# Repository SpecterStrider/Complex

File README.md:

# Project COMPLEX
Complex is a 36-key ergonomic split keyboard inspired by  

Corne by foostan and  
https://github.com/foostan/crkbd/tree/main

Tempest by thrly  
https://github.com/thrly/tempest

## TO DO List
- [ ] Impedance match USB
- [ ] Right Side PCB
- [ ] include Case and 3d files
- [ ] Rebase from kiCAD to Fusion ECAD
- [ ] Begin QMK firmware
- [ ] define COMPLEX.cpp in QMK environment
- [ ] create Keyamp

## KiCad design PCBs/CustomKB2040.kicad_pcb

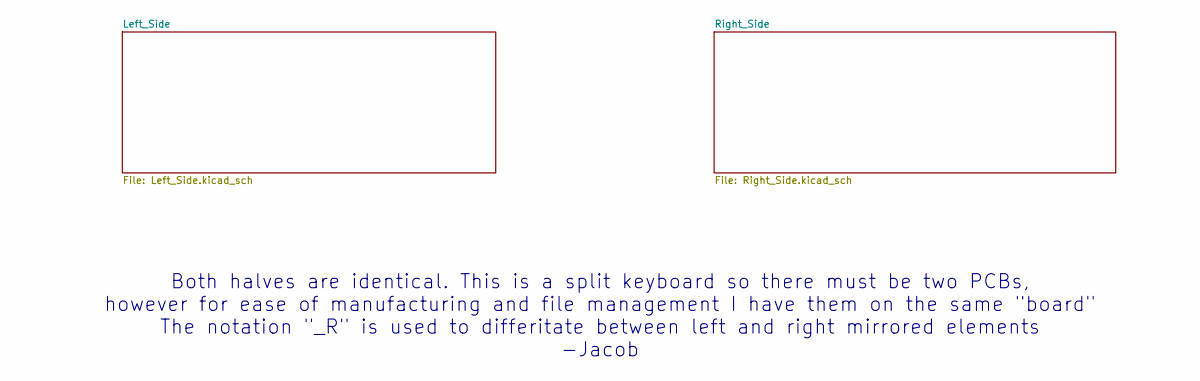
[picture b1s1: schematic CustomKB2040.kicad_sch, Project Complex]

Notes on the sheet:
Both halves are identical. This is a split keyboard so there must be two PCBs, however for ease of manufacturing and file management I have them on the same "board" The notation "_R" is used to differitate between left and right mirrored elements -Jacob

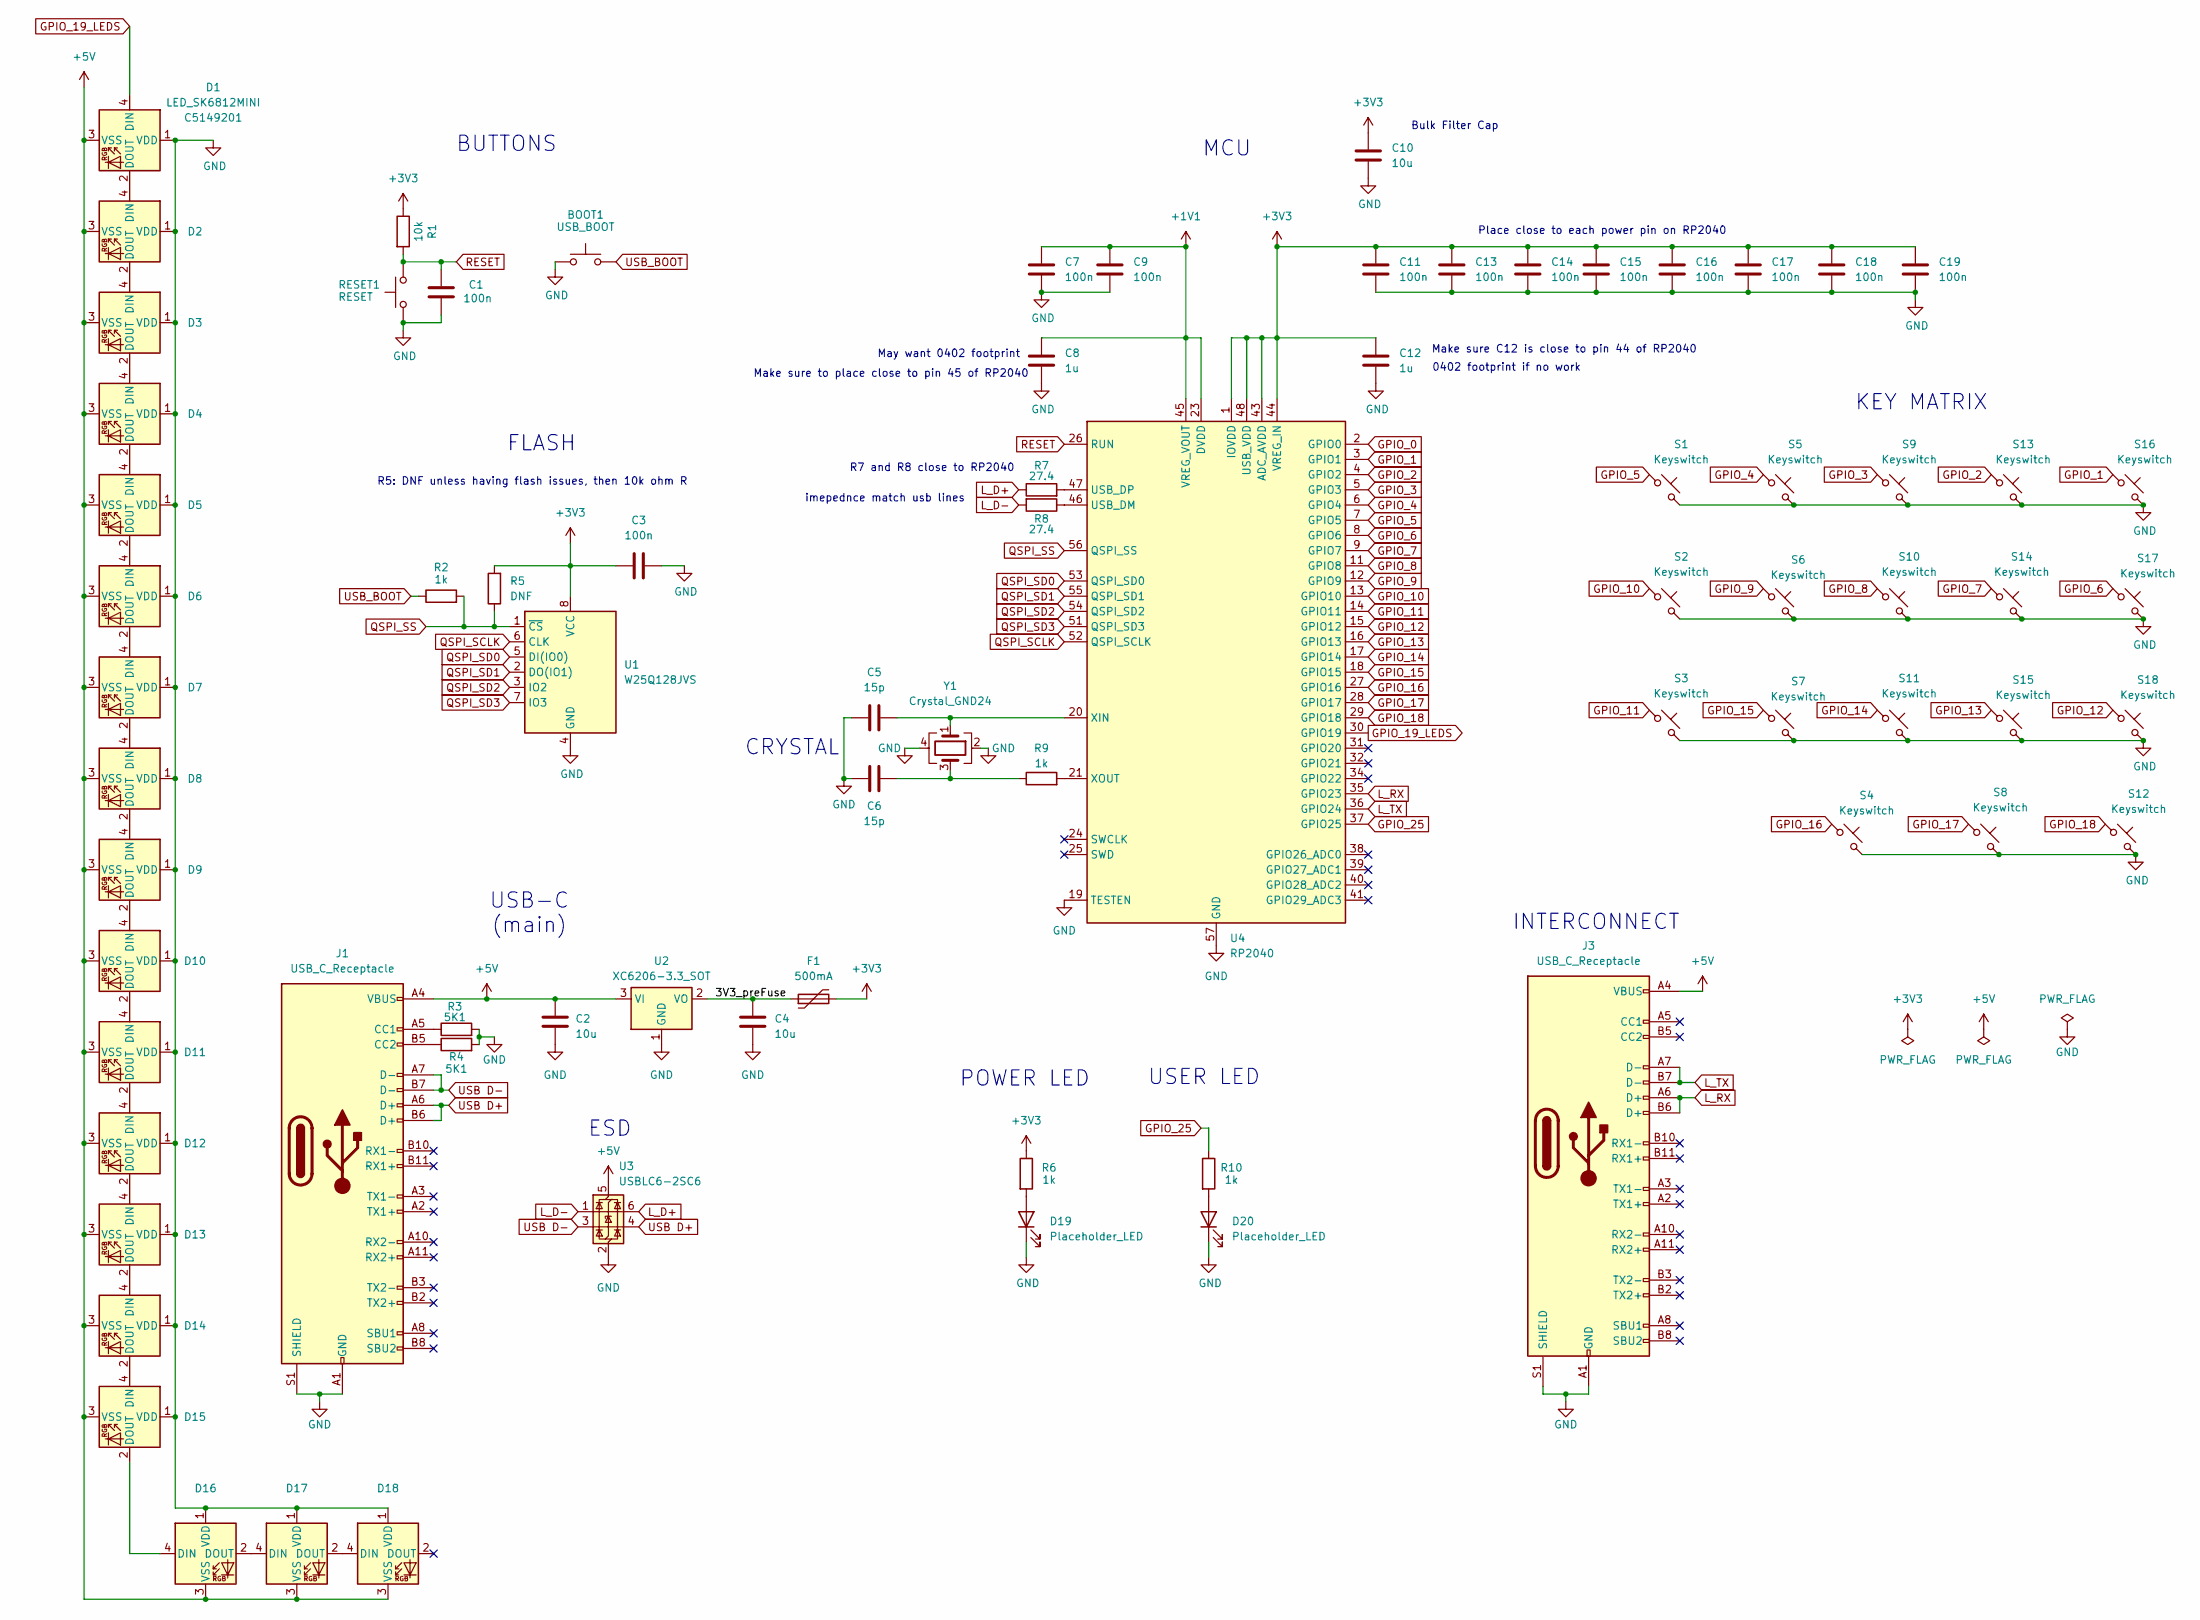
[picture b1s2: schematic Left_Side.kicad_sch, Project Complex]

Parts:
BOOT1: USB_BOOT; SW_Push_1P1T_NO_CK_KMR2
C1, C3, C7, C9, C11, C13, C14, C15, C16, C17, C18, C19: 100n; C_0603_1608Metric
C2, C4, C10: 10u; C_0603_1608Metric
C5, C6: 15p; C_0603_1608Metric
C8, C12: 1u; C_0603_1608Metric
D1, D2, D3, D4, D5, D6, D7, D8, D9, D10, D11, D12, D13, D14, D15, D16, D17, D18: LED_SK6812MINI; LCSC C5149201
D19, D20: Placeholder_LED; LED_0805
F1: 500mA; Fuse_0603
J1, J3: USB_C_Receptacle; USB_C_Receptacle_HRO_TYPE-C-31-M-12
R1: 10k; R_0603_1608Metric
R2, R6, R9, R10: 1k; R_0603_1608Metric
R3, R4: 5K1; R_0603_1608Metric
R5: DNF; R_0603_1608Metric
R7, R8: 27.4; R_0603_1608Metric
RESET1: RESET; SW_Push_1P1T_NO_CK_KMR2
S1, S2, S3, S4, S5, S6, S7, S8, S9, S10, S11, S12, S13, S14, S15, S16, S17, S18: Keyswitch; Hotswap_Choc_V2_Plated_1.00u
U1: W25Q128JVS; SOIC-8_5.23x5.23mm_P1.27mm
U2: XC6206-3.3_SOT; Voltage_SOT-23
U3: USBLC6-2SC6; SOT-23-6
U4: RP2040; QFN-56-1EP_7x7mm_P0.4mm_EP3.2x3.2mm
Y1: Crystal_GND24; Crystal_SMD_Abracon_ABM8G-4Pin_3.2x2.5mm

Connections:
+1V1: C7.1, C8.1, C9.1, U4.23 (DVDD), U4.45 (VREG_VOUT), U4.50 (DVDD)
+3V3: C3.1, C10.1, C11.1, C12.1, C13.1, C14.1, C15.1, C16.1, C17.1, C18.1, C19.1, F1.2, R1.1, R5.2, R6.1, U1.8 (VCC), U4.1 (IOVDD), U4.10 (IOVDD), U4.22 (IOVDD), U4.33 (IOVDD), U4.42 (IOVDD), U4.43 (ADC_AVDD), U4.44 (VREG_IN), U4.48 (USB_VDD), U4.49 (IOVDD)
+5V: C2.1, D1.3 (VSS), D2.3 (VSS), D3.3 (VSS), D4.3 (VSS), D5.3 (VSS), D6.3 (VSS), D7.3 (VSS), D8.3 (VSS), D9.3 (VSS), D10.3 (VSS), D11.3 (VSS), D12.3 (VSS), D13.3 (VSS), D14.3 (VSS), D15.3 (VSS), D16.3 (VSS), D17.3 (VSS), D18.3 (VSS), J1.A4 (VBUS), J1.A9 (VBUS), J1.B4 (VBUS), J1.B9 (VBUS), J3.A4 (VBUS), J3.A9 (VBUS), J3.B4 (VBUS), J3.B9 (VBUS), U2.3 (VI), U3.5 (VBUS)
/Left_Side/3V3_preFuse: C4.1, F1.1, U2.2 (VO)
GND: BOOT1.1, C1.1, C2.2, C3.2, C4.2, C5.2, C6.2, C7.2, C8.2, C9.2, C10.2, C11.2, C12.2, C13.2, C14.2, C15.2, C16.2, C17.2, C18.2, C19.2, D1.1 (VDD), D2.1 (VDD), D3.1 (VDD), D4.1 (VDD), D5.1 (VDD), D6.1 (VDD), D7.1 (VDD), D8.1 (VDD), D9.1 (VDD), D10.1 (VDD), D11.1 (VDD), D12.1 (VDD), D13.1 (VDD), D14.1 (VDD), D15.1 (VDD), D16.1 (VDD), D17.1 (VDD), D18.1 (VDD), D19.1 (K), D20.1 (K), J1.A1 (GND), J1.A12 (GND), J1.B1 (GND), J1.B12 (GND), J1.S1 (SHIELD), J3.A1 (GND), J3.A12 (GND), J3.B1 (GND), J3.B12 (GND), J3.S1 (SHIELD), R3.2, R4.2, RESET1.1, S1.2, S2.2, S3.2, S4.2, S5.2, S6.2, S7.2, S8.2, S9.2, S10.2, S11.2, S12.2, S13.2, S14.2, S15.2, S16.2, S17.2, S18.2, U1.4 (GND), U2.1 (GND), U3.2 (GND), U4.19 (TESTEN), U4.57 (GND), Y1.2, Y1.4
GPIO_0: U4.2 (GPIO0)
GPIO_1: S16.1, U4.3 (GPIO1)
GPIO_2: S13.1, U4.4 (GPIO2)
GPIO_3: S9.1, U4.5 (GPIO3)
GPIO_4: S5.1, U4.6 (GPIO4)
GPIO_5: S1.1, U4.7 (GPIO5)
GPIO_6: S17.1, U4.8 (GPIO6)
GPIO_7: S14.1, U4.9 (GPIO7)
GPIO_8: S10.1, U4.11 (GPIO8)
GPIO_9: S6.1, U4.12 (GPIO9)
GPIO_10: S2.1, U4.13 (GPIO10)
GPIO_11: S3.1, U4.14 (GPIO11)
GPIO_12: S18.1, U4.15 (GPIO12)
GPIO_13: S15.1, U4.16 (GPIO13)
GPIO_14: S11.1, U4.17 (GPIO14)
GPIO_15: S7.1, U4.18 (GPIO15)
GPIO_16: S4.1, U4.27 (GPIO16)
GPIO_17: S8.1, U4.28 (GPIO17)
GPIO_18: S12.1, U4.29 (GPIO18)
GPIO_19_LEDS: D1.4 (DIN), U4.30 (GPIO19)
GPIO_25: R10.1, U4.37 (GPIO25)
L_D+: R7.1, U3.6 (I/O1)
L_D-: R8.2, U3.1 (I/O1)
L_RX: J3.A6 (D+), J3.B6 (D+), U4.35 (GPIO23)
L_TX: J3.A7 (D-), J3.B7 (D-), U4.36 (GPIO24)
unnamed: C6.1, R9.1, Y1.3
unnamed: D1.2 (DOUT), D2.4 (DIN)
unnamed: D2.2 (DOUT), D3.4 (DIN)
unnamed: D3.2 (DOUT), D4.4 (DIN)
unnamed: D4.2 (DOUT), D5.4 (DIN)
unnamed: D5.2 (DOUT), D6.4 (DIN)
unnamed: D6.2 (DOUT), D7.4 (DIN)
unnamed: D7.2 (DOUT), D8.4 (DIN)
unnamed: D8.2 (DOUT), D9.4 (DIN)
unnamed: D9.2 (DOUT), D10.4 (DIN)
unnamed: D10.2 (DOUT), D11.4 (DIN)
unnamed: D11.2 (DOUT), D12.4 (DIN)
unnamed: D12.2 (DOUT), D13.4 (DIN)
unnamed: D13.2 (DOUT), D14.4 (DIN)
unnamed: D14.2 (DOUT), D15.4 (DIN)
unnamed: D15.2 (DOUT), D16.4 (DIN)
unnamed: D16.2 (DOUT), D17.4 (DIN)
unnamed: D17.2 (DOUT), D18.4 (DIN)
unnamed: D19.2 (A), R6.2
unnamed: D20.2 (A), R10.2
unnamed: J1.A5 (CC1), R3.1
unnamed: J1.B5 (CC2), R4.1
unnamed: R8.1, U4.46 (USB_DM)
unnamed: R7.2, U4.47 (USB_DP)
unnamed: C5.1, U4.20 (XIN), Y1.1
unnamed: R9.2, U4.21 (XOUT)
QSPI_SCLK: U1.6 (CLK), U4.52 (QSPI_SCLK)
QSPI_SD0: U1.5 (DI(IO0)), U4.53 (QSPI_SD0)
QSPI_SD1: U1.2 (DO(IO1)), U4.55 (QSPI_SD1)
QSPI_SD2: U1.3 (IO2), U4.54 (QSPI_SD2)
QSPI_SD3: U1.7 (IO3), U4.51 (QSPI_SD3)
QSPI_SS: R2.2, R5.1, U1.1 (~CS), U4.56 (QSPI_SS)
RESET: C1.2, R1.2, RESET1.2, U4.26 (RUN)
USB D+: J1.A6 (D+), J1.B6 (D+), U3.4 (I/O2)
USB D-: J1.A7 (D-), J1.B7 (D-), U3.3 (I/O2)
USB_BOOT: BOOT1.2, R2.1

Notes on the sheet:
MCU
Bulk Filter Cap
Make sure C12 is close to pin 44 of RP2040
USER LED
POWER LED
FLASH
ESD
R7 and R8 close to RP2040
CRYSTAL
May want 0402 footprint
INTERCONNECT
BUTTONS
Make sure to place close to pin 45 of RP2040
R5: DNF unless having flash issues, then 10k ohm R
imepednce match usb lines
USB-C (main)
0402 footprint if no work
Place close to each power pin on RP2040
KEY MATRIX

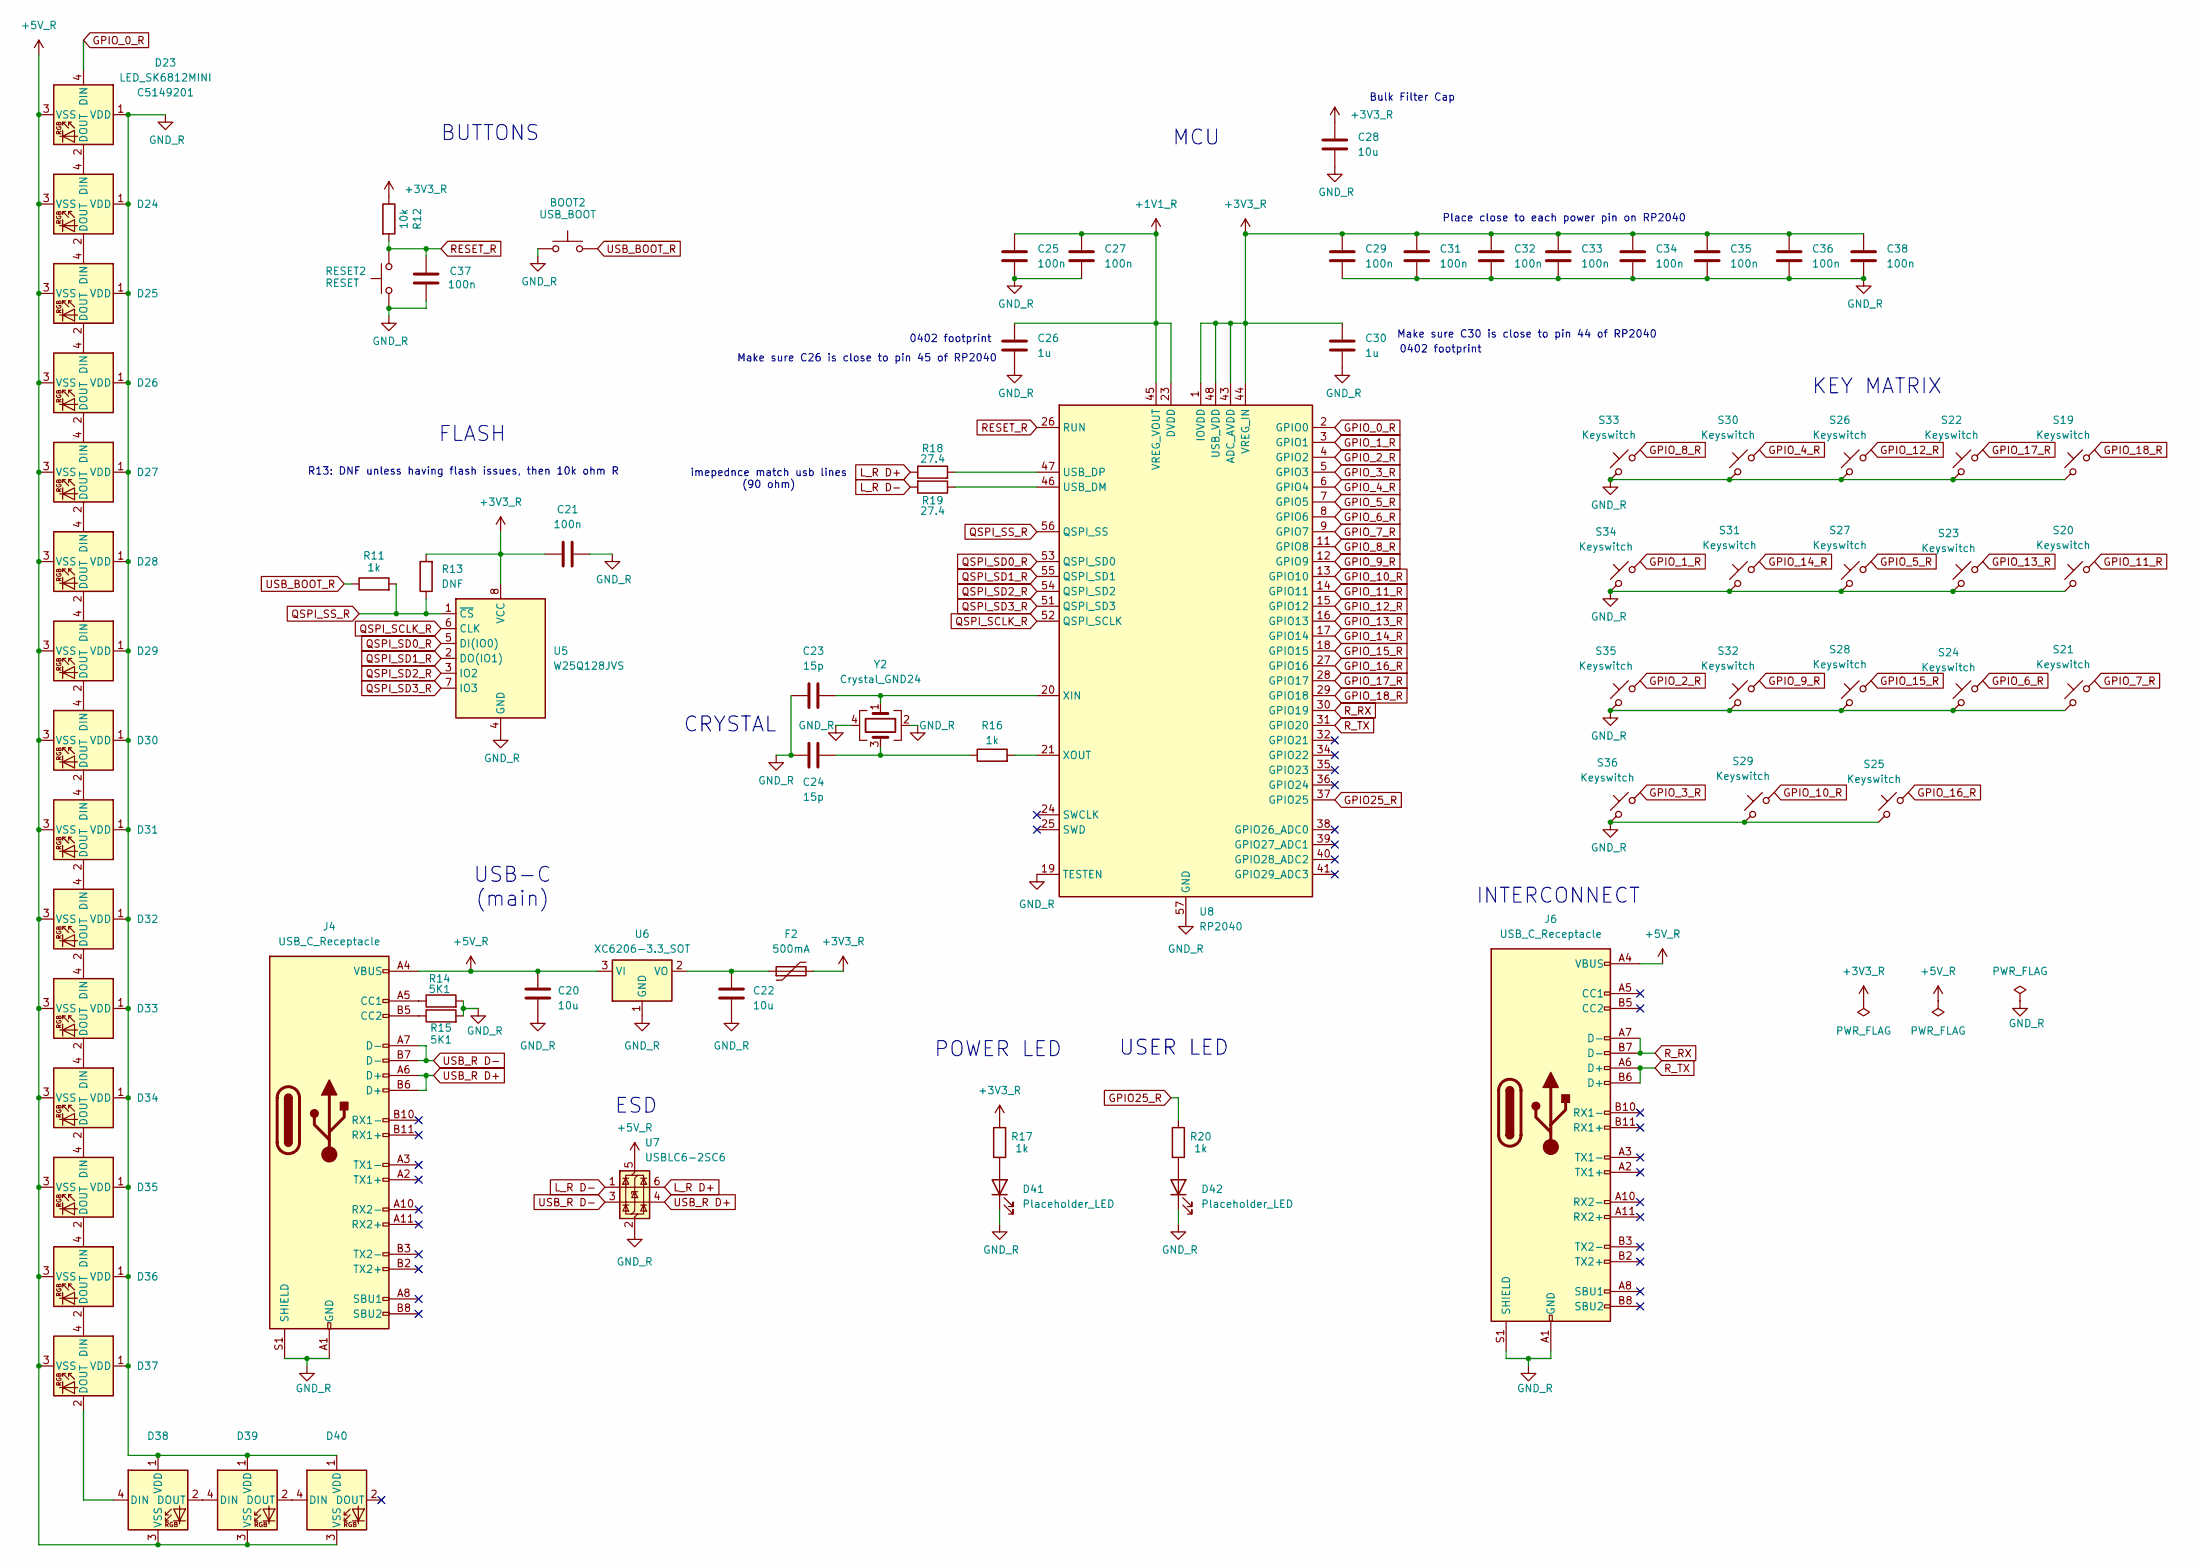
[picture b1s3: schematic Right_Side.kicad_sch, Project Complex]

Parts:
BOOT2: USB_BOOT; SW_Push_1P1T_NO_CK_KMR2
C20, C22, C28: 10u; C_0603_1608Metric
C21, C25, C27, C29, C31, C32, C33, C34, C35, C36, C37, C38: 100n; C_0603_1608Metric
C23, C24: 15p; C_0603_1608Metric
C26, C30: 1u; C_0603_1608Metric
D23, D24, D25, D26, D27, D28, D29, D30, D31, D32, D33, D34, D35, D36, D37, D38, D39, D40: LED_SK6812MINI; LCSC C5149201
D41, D42: Placeholder_LED; LED_0805
F2: 500mA; Fuse_0603
J4, J6: USB_C_Receptacle; USB_C_Receptacle_HRO_TYPE-C-31-M-12
R11, R16, R17, R20: 1k; R_0603_1608Metric
R12: 10k; R_0603_1608Metric
R13: DNF; R_0603_1608Metric
R14, R15: 5K1; R_0603_1608Metric
R18, R19: 27.4; R_0603_1608Metric
RESET2: RESET; SW_Push_1P1T_NO_CK_KMR2
S19, S20, S21, S22, S23, S24, S25, S26, S27, S28, S29, S30, S31, S32, S33, S34, S35, S36: Keyswitch; Hotswap_Choc_V2_Plated_1.00u
U5: W25Q128JVS; SOIC-8_5.23x5.23mm_P1.27mm
U6: XC6206-3.3_SOT; Voltage_SOT-23
U7: USBLC6-2SC6; SOT-23-6
U8: RP2040; QFN-56-1EP_7x7mm_P0.4mm_EP3.2x3.2mm
Y2: Crystal_GND24; Crystal_SMD_Abracon_ABM8G-4Pin_3.2x2.5mm

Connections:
+1V1_R: C25.1, C26.1, C27.1, U8.23 (DVDD), U8.45 (VREG_VOUT), U8.50 (DVDD)
+3V3_R: C21.1, C28.1, C29.1, C30.1, C31.1, C32.1, C33.1, C34.1, C35.1, C36.1, C38.1, F2.2, R12.1, R13.2, R17.1, U5.8 (VCC), U8.1 (IOVDD), U8.10 (IOVDD), U8.22 (IOVDD), U8.33 (IOVDD), U8.42 (IOVDD), U8.43 (ADC_AVDD), U8.44 (VREG_IN), U8.48 (USB_VDD), U8.49 (IOVDD)
+5V_R: C20.1, D23.3 (VSS), D24.3 (VSS), D25.3 (VSS), D26.3 (VSS), D27.3 (VSS), D28.3 (VSS), D29.3 (VSS), D30.3 (VSS), D31.3 (VSS), D32.3 (VSS), D33.3 (VSS), D34.3 (VSS), D35.3 (VSS), D36.3 (VSS), D37.3 (VSS), D38.3 (VSS), D39.3 (VSS), D40.3 (VSS), J4.A4 (VBUS), J4.A9 (VBUS), J4.B4 (VBUS), J4.B9 (VBUS), J6.A4 (VBUS), J6.A9 (VBUS), J6.B4 (VBUS), J6.B9 (VBUS), U6.3 (VI), U7.5 (VBUS)
GND_R: BOOT2.1, C20.2, C21.2, C22.2, C23.2, C24.2, C25.2, C26.2, C27.2, C28.2, C29.2, C30.2, C31.2, C32.2, C33.2, C34.2, C35.2, C36.2, C37.1, C38.2, D23.1 (VDD), D24.1 (VDD), D25.1 (VDD), D26.1 (VDD), D27.1 (VDD), D28.1 (VDD), D29.1 (VDD), D30.1 (VDD), D31.1 (VDD), D32.1 (VDD), D33.1 (VDD), D34.1 (VDD), D35.1 (VDD), D36.1 (VDD), D37.1 (VDD), D38.1 (VDD), D39.1 (VDD), D40.1 (VDD), D41.1 (K), D42.1 (K), J4.A1 (GND), J4.A12 (GND), J4.B1 (GND), J4.B12 (GND), J4.S1 (SHIELD), J6.A1 (GND), J6.A12 (GND), J6.B1 (GND), J6.B12 (GND), J6.S1 (SHIELD), R14.2, R15.2, RESET2.1, S19.2, S20.2, S21.2, S22.2, S23.2, S24.2, S25.2, S26.2, S27.2, S28.2, S29.2, S30.2, S31.2, S32.2, S33.2, S34.2, S35.2, S36.2, U5.4 (GND), U6.1 (GND), U7.2 (GND), U8.19 (TESTEN), U8.57 (GND), Y2.2, Y2.4
GPIO25_R: R20.1, U8.37 (GPIO25)
GPIO_0_R: D23.4 (DIN), U8.2 (GPIO0)
GPIO_1_R: S34.1, U8.3 (GPIO1)
GPIO_2_R: S35.1, U8.4 (GPIO2)
GPIO_3_R: S36.1, U8.5 (GPIO3)
GPIO_4_R: S30.1, U8.6 (GPIO4)
GPIO_5_R: S27.1, U8.7 (GPIO5)
GPIO_6_R: S24.1, U8.8 (GPIO6)
GPIO_7_R: S21.1, U8.9 (GPIO7)
GPIO_8_R: S33.1, U8.11 (GPIO8)
GPIO_9_R: S32.1, U8.12 (GPIO9)
GPIO_10_R: S29.1, U8.13 (GPIO10)
GPIO_11_R: S20.1, U8.14 (GPIO11)
GPIO_12_R: S26.1, U8.15 (GPIO12)
GPIO_13_R: S23.1, U8.16 (GPIO13)
GPIO_14_R: S31.1, U8.17 (GPIO14)
GPIO_15_R: S28.1, U8.18 (GPIO15)
GPIO_16_R: S25.1, U8.27 (GPIO16)
GPIO_17_R: S22.1, U8.28 (GPIO17)
GPIO_18_R: S19.1, U8.29 (GPIO18)
L_R D+: R18.1, U7.6 (I/O1)
L_R D-: R19.2, U7.1 (I/O1)
unnamed: C24.1, R16.1, Y2.3
unnamed: D23.2 (DOUT), D24.4 (DIN)
unnamed: D24.2 (DOUT), D25.4 (DIN)
unnamed: D25.2 (DOUT), D26.4 (DIN)
unnamed: D26.2 (DOUT), D27.4 (DIN)
unnamed: D27.2 (DOUT), D28.4 (DIN)
unnamed: D28.2 (DOUT), D29.4 (DIN)
unnamed: D29.2 (DOUT), D30.4 (DIN)
unnamed: D30.2 (DOUT), D31.4 (DIN)
unnamed: D31.2 (DOUT), D32.4 (DIN)
unnamed: D32.2 (DOUT), D33.4 (DIN)
unnamed: D33.2 (DOUT), D34.4 (DIN)
unnamed: D34.2 (DOUT), D35.4 (DIN)
unnamed: D35.2 (DOUT), D36.4 (DIN)
unnamed: D36.2 (DOUT), D37.4 (DIN)
unnamed: D37.2 (DOUT), D38.4 (DIN)
unnamed: D38.2 (DOUT), D39.4 (DIN)
unnamed: D39.2 (DOUT), D40.4 (DIN)
unnamed: D41.2 (A), R17.2
unnamed: D42.2 (A), R20.2
unnamed: J4.A5 (CC1), R14.1
unnamed: J4.B5 (CC2), R15.1
unnamed: C22.1, F2.1, U6.2 (VO)
unnamed: R19.1, U8.46 (USB_DM)
unnamed: R18.2, U8.47 (USB_DP)
unnamed: C23.1, U8.20 (XIN), Y2.1
unnamed: R16.2, U8.21 (XOUT)
QSPI_SCLK_R: U5.6 (CLK), U8.52 (QSPI_SCLK)
QSPI_SD0_R: U5.5 (DI(IO0)), U8.53 (QSPI_SD0)
QSPI_SD1_R: U5.2 (DO(IO1)), U8.55 (QSPI_SD1)
QSPI_SD2_R: U5.3 (IO2), U8.54 (QSPI_SD2)
QSPI_SD3_R: U5.7 (IO3), U8.51 (QSPI_SD3)
QSPI_SS_R: R11.2, R13.1, U5.1 (~CS), U8.56 (QSPI_SS)
RESET_R: C37.2, R12.2, RESET2.2, U8.26 (RUN)
R_RX: J6.A7 (D-), J6.B7 (D-), U8.30 (GPIO19)
R_TX: J6.A6 (D+), J6.B6 (D+), U8.31 (GPIO20)
USB_BOOT_R: BOOT2.2, R11.1
USB_R D+: J4.A6 (D+), J4.B6 (D+), U7.4 (I/O2)
USB_R D-: J4.A7 (D-), J4.B7 (D-), U7.3 (I/O2)

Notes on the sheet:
Make sure C30 is close to pin 44 of RP2040
0402 footprint
CRYSTAL
R13: DNF unless having flash issues, then 10k ohm R
MCU
KEY MATRIX
imepednce match usb lines (90 ohm)
POWER LED
Bulk Filter Cap
ESD
Place close to each power pin on RP2040
USB-C (main)
INTERCONNECT
USER LED
FLASH
Make sure C26 is close to pin 45 of RP2040
BUTTONS

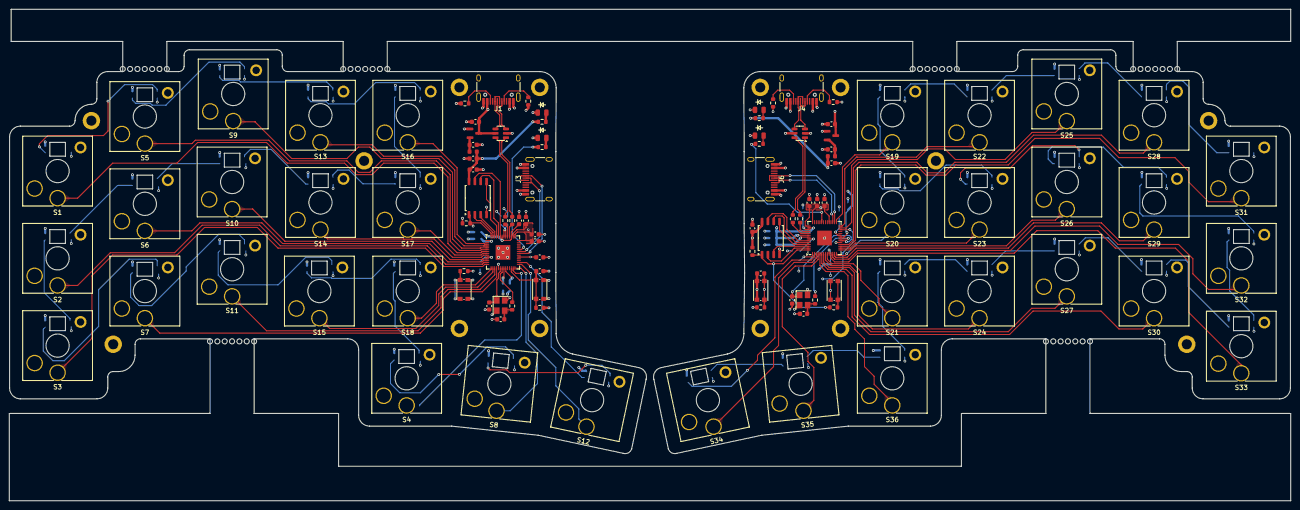
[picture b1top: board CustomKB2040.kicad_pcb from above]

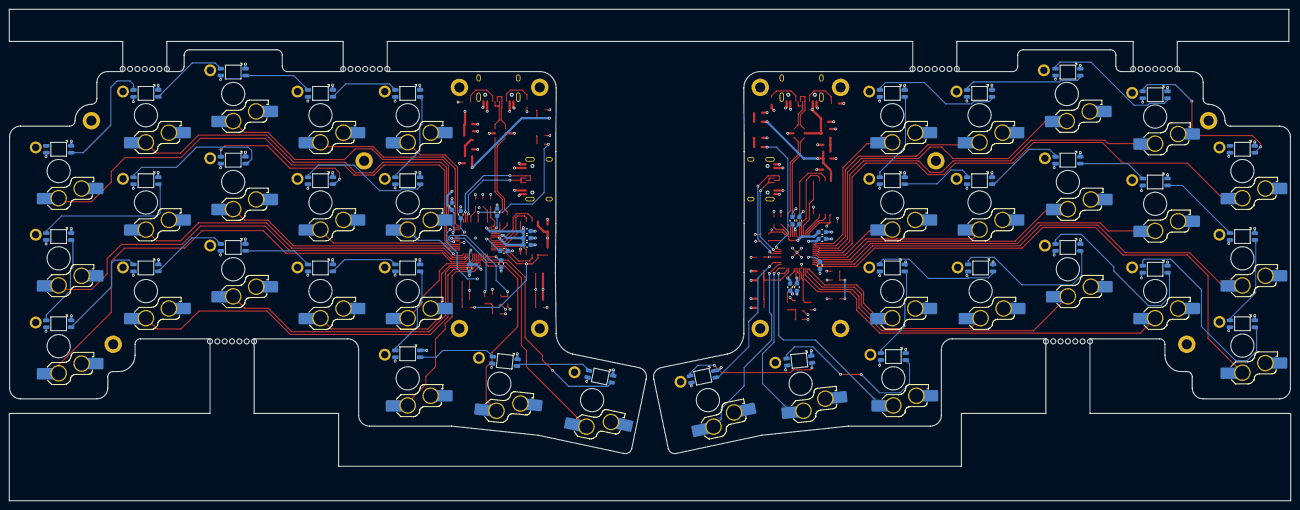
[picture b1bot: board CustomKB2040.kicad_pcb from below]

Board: 4 copper layers, 279.0 x 107.0 mm, 154 parts (52 on the bottom side), 130 nets.

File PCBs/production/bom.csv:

Designator,Footprint,Quantity,Value,LCSC Part #
"_3, _2, ",,3,,
"BOOT1, BOOT2",SW_Push_1P1T_NO_CK_KMR2,2,USB_BOOT,
"C1, C11, C13, C14, C15, C16, C17, C18, C19, C21, C25, C27, C29, C3, C31, C32, C33, C34, C35, C36, C37, C38, C7, C9",0603,24,100n,
"C10, C2, C20, C22, C28, C4",0603,6,10u,
"C12, C26, C30, C8",0603,4,1u,
"C23, C24, C5, C6",0603,4,15p,
"D1, D10, D11, D12, D13, D14, D15, D16, D17, D18, D2, D23, D24, D25, D26, D27, D28, D29, D3, D30, D31, D32, D33, D34, D35, D36, D37, D38, D39, D4, D40, D5, D6, D7, D8, D9",LED_SK6812MINI,36,LED_SK6812MINI,C5149201
"D19, D20, D41, D42",LED_0805,4,Placeholder_LED,
"F1, F2",Fuse_0603,2,500mA,
"J1, J3, J4, J6",USB_C_Receptacle_HRO_TYPE-C-31-M-12,4,USB_C_Receptacle,
"R1, R12",0603,2,10k,
"R10, R11, R16, R17, R2, R20, R6, R9",0603,8,1k,
"R13, R5",0603,2,DNF,
"R14, R15, R3, R4",0603,4,5K1,
"R18, R19, R7, R8",0603,4,27.4,
"RESET1, RESET2",SW_Push_1P1T_NO_CK_KMR2,2,RESET,
"S1, S10, S11, S12, S13, S14, S15, S16, S17, S18, S19, S2, S20, S21, S22, S23, S24, S25, S26, S27, S28, S29, S3, S30, S31, S32, S33, S34, S35, S36, S4, S5, S6, S7, S8, S9",Hotswap_Choc_V2_Plated_1.00u,36,Keyswitch,
"U1, U5",SOIC-8_5.23x5.23mm_P1.27mm,2,W25Q128JVS,
"U2, U6",Voltage_SOT-23,2,XC6206-3.3_SOT,
"U3, U7",SOT-23-6,2,USBLC6-2SC6,
"U4, U8",QFN-56-1EP_7x7mm_P0.4mm_EP3.2x3.2mm,2,RP2040,
"Y1, Y2",Crystal_SMD_Abracon_ABM8G-4Pin_3.2x2.5mm,2,Crystal_GND24,

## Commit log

2025-07-27 added MCU to images
2025-07-27 added overall img
2025-08-06 placed companets and semi routed
2025-08-13 added 5v pads
2025-08-13 why is this not working
2025-08-25 converted to 4 layer board
2025-08-26 Finished left side
2025-08-26 added PCB image
2025-08-26 resturctured repo
2025-09-26 began right side
2025-09-26 store for replacement
2025-09-27 trying to sync
2025-09-29 near complete right side
2025-10-05 mid way right side
2025-10-08 edge outline done
2025-10-24 making progress
2025-10-24 Update TO DO list to include Case and 3D files
2025-11-25 arragned right side
2025-11-29 added library and routing changes
